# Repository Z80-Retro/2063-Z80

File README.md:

# Retro Z80 CPU Board

This project was designed to run CP/M 2.2 from an SD card.  It should be an attainable goal for anyone that can solder through-hole parts to assemble it. Note that J10 is an optional header that allows a Sparkfun SD card breakout board [DEV-13743](https://www.digikey.com/en/products/detail/sparkfun-electronics/DEV-13743/5881845) to used instead of soldering on the surface-mount SD socket part.

Here is an easy-to-find direct link to the [PDF of the schematic](https://github.com/Z80-Retro/2063-Z80/raw/main/2063-Z80.pdf) for a quick view.

## Where to get Boards & Software

* You can order boards from any prototype PCB vendor.  For example, I show how you can order these boards from [JLCPCB](https://jlcpcb.com/) or [OSHPark](https://oshpark.com/) by uploading the gerber files found in the releases of this and the flash programmer projects as shown in this [Z80 Retro! - How To Order PC Boards](https://youtu.be/AUg_sbPnzn0) video on YouTube.
  - Gerber files for the CPU board: [2063-Z80-v3](https://github.com/johnwinans/2063-Z80/releases/download/v3/2063-Z80-gerbers.zip)
  - Gerber files for the FLASH programmer: [2065-Z80-programmer-v2](https://github.com/johnwinans/2065-Z80-programmer/releases/download/v2.0/2065-Z80-programmer-gerbers.zip) (This is used with a Raspberry PI to program the FLASH chip on the CPU board.)

* Software for this project can be found in my [2063-Z80-cpm](https://github.com/johnwinans/2063-Z80-cpm) repo.

* Note that the [FLASH programmer](https://github.com/johnwinans/2065-Z80-programmer) has been designed to work with a Raspberry PI in the event that you don't already own such programmer.  This companion programmer PCB should cost about $2 more when it is ordered at the same time as the CPU board from JLCPCB or other similar proto-board shops as shown in the [Z80 Retro! - How To Order PC Boards](https://youtu.be/AUg_sbPnzn0) video on YouTube.

## Links to Related Material

* A youtube playlist discussing this project and how to build your own can be found in [John's Basement](https://www.youtube.com/watch?v=oekucjDcNbA&list=PL3by7evD3F51Cf9QnsAEdgSQ4cz7HQZX5)
* A PDF version of the schematic can be found [here](2063-Z80.pdf).
* Here is the as-built [BOM](2063-Z80.md) with links to the datasheets for all the parts.
* Here is another [BOM](2063-Z80-sockets.md) with links to sockets for the chips.
* To configure a new PI for use with this programmer board as well as to develop Z80 code 
for the Z80 Retro board, see this [PI Setup Guide](https://github.com/johnwinans/raspberry-pi-install)
* More software for this project will be added as it evolves.

## Links to Related Datasheets Seen On YouTube

* [Z80 Datasheet PS0178](https://www.zilog.com/docs/z80/ps0178.pdf) with detailed timing diagrams.
* [Z80 User Manual UM0080](http://www.zilog.com/docs/z80/um0080.pdf) with detailed descriptions of each instruction.
* [Z80 Assembly Language Programming Manual](http://zxevo.ru/inc/Zilog_Z80_assembly_language_programming_classic.pdf) - The original version of the instructions without the OCR errors present in UM0080.
* [Z80 CPU Peripherals User Manual UM0081](http://www.zilog.com/docs/z80/um0081.pdf) discusses the CTC and SIO.
* [Z80 Family Product Specifications Handbook - 1984](http://www.bitsavers.org/components/zilog/z80/Z80_Family_Product_Specifications_Handbook_Feb84.pdf) has nicer pictures of the SIO registers.
* [Wikipedia UART Article](https://en.wikipedia.org/wiki/Universal_asynchronous_receiver-transmitter)
* [AY-3-1015D UART Datasheet](https://rocelec.widen.net/view/pdf/bvesdj0cqf/GSIIS01845-1.pdf) (Has a discussion of the 16X bit-rate clock with diagrams etc. applicable to all UARTs.)

## Serial Port Cable Parts

* [How to make IDC cables](https://youtu.be/gZ420Z-8HuU) for the serial ports.
* [IDC 2x5 connectors](https://www.amazon.com/gp/product/B07S1NFG4S)
* [IDC D-SUB 9-pin connectors (Digikey)](https://www.digikey.com/en/products/detail/assmann-wsw-components/A-DSF-09LPIII-Z/924263)
* [IDC D-SUB 9-pin connectors (Amazon)](https://www.amazon.com/Uxcell-a15030600ux0494-Female-Connector-Ribbon/dp/B00YM41NTW)

## Parallel Port Cable Parts

* [IDC 2x13 connectors](https://www.amazon.com/gp/product/B07RXK96GV)
* [IDC D-SUB 25-pin connectors (Digikey)](https://www.digikey.com/en/products/detail/amphenol-icc-commercial-products/L17DBFRA25S/1972210)
* [IDC D-SUB 25-pin connectors (Amazon)](https://www.amazon.com/Fielect-Female-Adapter-Connector-Ribbon/dp/B082GMDNTS)

## Ribbon Cable

* [40-conductor (Amazon)](https://www.amazon.com/Eowpower-40Pin-40Way-Rainbow-Ribbon/dp/B079KQ6K3Y) - peel off a
 26-pin strip and a 10-pin strip to make one parallel and one serial cable (cut the 10-pin strip in half length-wise to make two serial cables.

# Release Notes

## V4.4.0

- Change footprint for SD socket to increase the pad size for mounting the case.
- Label R15 and R16 as DNP.
- Move the [diffs](./diffs/) into their own directory.
- V4.3.3 to V4.4.0 schematic [visual diff](https://github.com/Z80-Retro/2063-Z80/raw/main/diffs/2063-Z80-V4.3.3-V4.4.0-delta-schematic.pdf)
- V4.3.3 to V4.4.0 PCB [visual diff](https://raw.githubusercontent.com/Z80-Retro/2063-Z80/main/diffs/2063-Z80-V4.3.3-V4.4.0-delta-pcb.png)

## V4.3.3

- Increase the values of the RS232 charge pump (on U12) capacitors to improve filtering.
- V4.3.2 V4.3.3 schematic [visual diff](https://github.com/Z80-Retro/2063-Z80/raw/main/diffs/2063-Z80-V4.3.2-V4.3.3-delta-schematic.pdf)
- V4.3.2 V4.3.3 PCB [visual diff](https://github.com/Z80-Retro/2063-Z80/raw/main/diffs/2063-Z80-V4.3.2-V4.3.3-delta-pcb.png) (no changes)

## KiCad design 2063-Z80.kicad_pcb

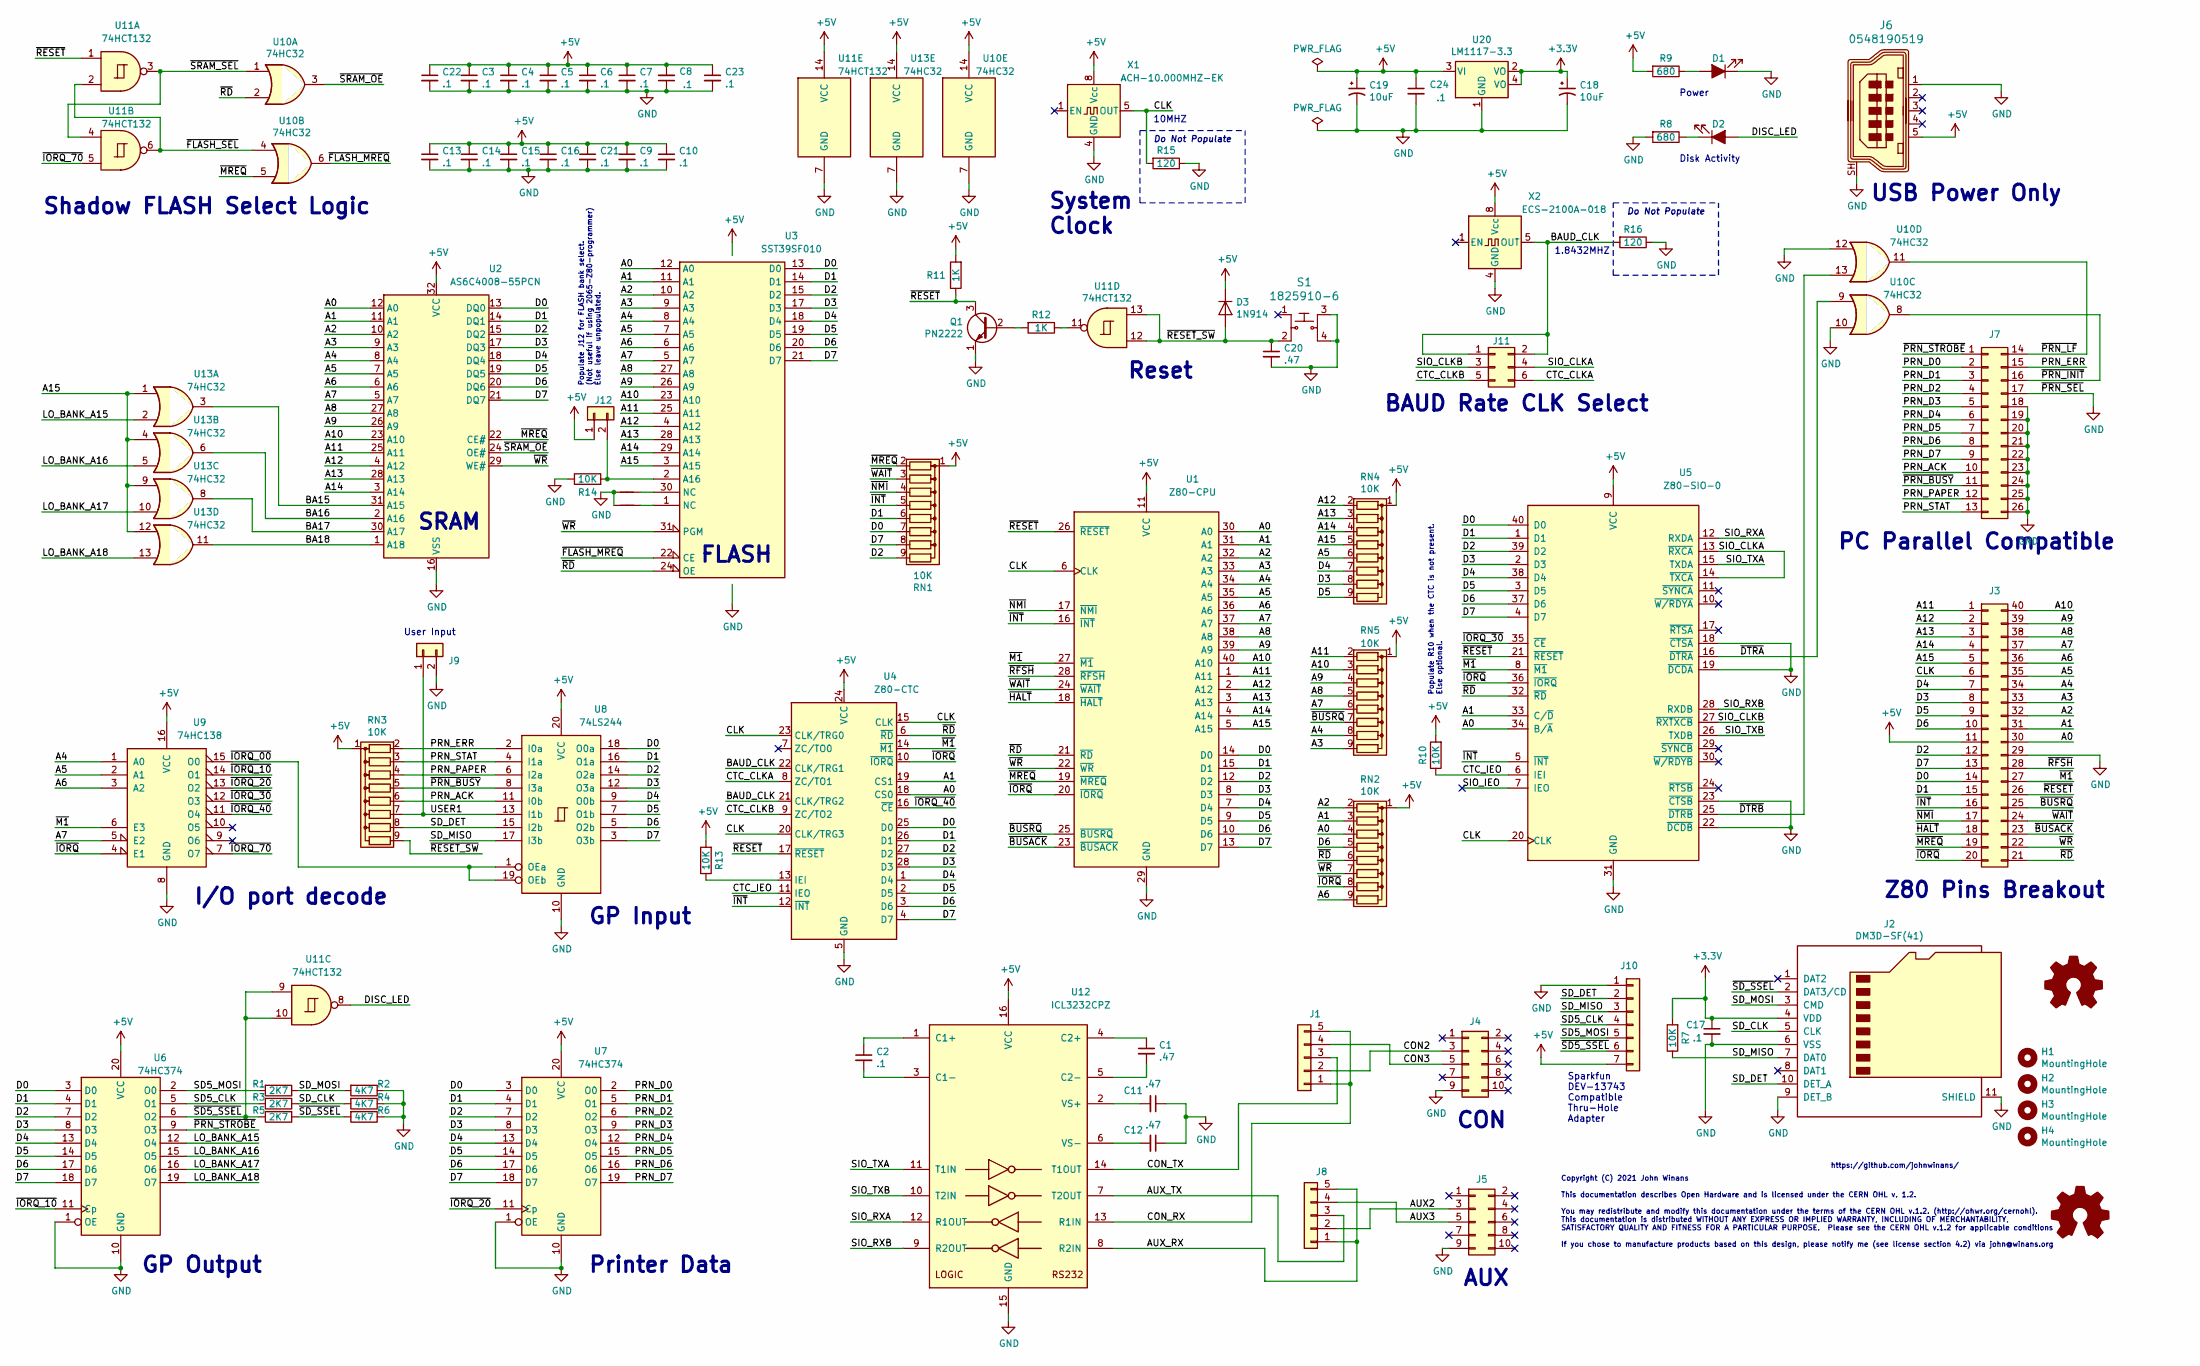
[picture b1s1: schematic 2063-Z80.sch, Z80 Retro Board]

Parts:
C1, C11, C12, C20: .47; C_Disc_D3.0mm_W2.0mm_P2.50mm; MPN C315C474K5R5TA7303; Digi-Key_PN 399-14039-1-ND
C2, C3, C4, C5, C6, C7, C8, C9, C10, C13, C14, C15, C16, C21, C22, C23: .1; C_Disc_D3.0mm_W2.0mm_P2.50mm; MPN ‎C315C104M5U5TA7303‎; Digi-Key_PN 399-9859-1-ND
C17: .1; C_0805_2012Metric_Pad1.18x1.45mm_HandSolder; MPN CL10B104KB8NNWC; Digi-Key_PN 1276-1935-1-ND
C18: 10uF; C_0805_2012Metric_Pad1.18x1.45mm_HandSolder; MPN CL21A106MQFNNNE; Digi-Key_PN 1276-1298-1-ND
C19: 10uF; CP_Radial_D5.0mm_P2.50mm; MPN ECE-A1EKS100; Digi-Key_PN P975-ND
C24: .1; C_0805_2012Metric_Pad1.15x1.40mm_HandSolder; MPN CL10B104KB8NNWC; Digi-Key_PN 1276-1935-1-ND
D1, D2: LED_ALT; LED_D3.0mm; MPN MV57640; Digi-Key_PN 1080-1122-ND
D3: 1N914; D_DO-35_SOD27_P7.62mm_Horizontal; MPN 1N4148TR; Digi-Key_PN 1N4148FSCT-ND
H1, H2, H3, H4: MountingHole; MountingHole_2.7mm
J1, J8: Conn_01x05; PinHeader_1x05_P2.54mm_Vertical; MPN PRPC005SAAN-RC; Digi-Key_PN S1011EC-05-ND
J2: DM3D-SF(41); microSD_HC_Hirose_DM3D-SF-bigpad; MPN ‎DM3D-SF(41)‎; Digi-Key_PN H126097CT-ND (alternate: 114-00841-68-1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
J3: Conn_02x20; PinHeader_2x20_P2.54mm_Vertical_counterclock; MPN PRPC020DAAN-RC; Digi-Key_PN S2011EC-20-ND
J4, J5: Conn_02x05; PinHeader_2x05_P2.54mm_Vertical; MPN PR20205VBDN; Digi-Key_PN 1849-1002-ND
J6: 0548190519; USB_Mini_B_Female_548190519; MPN 0548190519; Digi-Key_PN A135698-ND
J7: Conn_02x13; PinHeader_2x13_P2.54mm_Top_Bottom; MPN PRPC013DAAN-RC; Digi-Key_PN S2011EC-13-ND
J9, J12: Conn_01x02; PinHeader_1x02_P2.54mm_Vertical; MPN PRPC002SAAN-RC; Digi-Key_PN S1011EC-02-ND
J10: Conn_01x07; PinHeader_1x07_P2.54mm_Vertical; MPN PRPC007SAAN-RC; Digi-Key_PN S1011EC-07-ND
J11: Conn_02x03; PinHeader_2x03_P2.54mm_Vertical; MPN PH2-06-UA; Digi-Key_PN 2057-PH2-06-UA-ND
LOGO1: OSHW_Logo; OSHW-Logo_11.4x12mm_SilkScreen
LOGO2: OSHW_Logo; OSHW-Logo_5.7x6mm_SilkScreen
NT1, NT2: Net-Tie_2; NetTie-2_SMD_Pad0.5mm
Q1: PN2222; TO-92L; MPN PN2222A PBFREE; Digi-Key_PN 1514-PN2222APBFREE-ND
R1, R3, R5: 2K7; R_Axial_DIN0204_L3.6mm_D1.6mm_P5.08mm_Horizontal; MPN ‎CF18JT2K70‎; Digi-Key_PN CF18JT2K70CT-ND
R2, R4, R6: 4K7; R_Axial_DIN0204_L3.6mm_D1.6mm_P5.08mm_Horizontal; MPN ‎CF18JT4K70‎; Digi-Key_PN CF18JT4K70CT-ND
R7, R10, R13, R14: 10K; R_Axial_DIN0204_L3.6mm_D1.6mm_P5.08mm_Horizontal; MPN CF18JT10K0; Digi-Key_PN CF18JT10K0CT-ND
R8, R9: 680; R_Axial_DIN0204_L3.6mm_D1.6mm_P5.08mm_Horizontal; MPN ‎CF18JT680R‎; Digi-Key_PN CF18JT680RCT-ND‎
R11, R12: 1K; R_Axial_DIN0204_L3.6mm_D1.6mm_P5.08mm_Horizontal; MPN ‎CF18JT1K00‎; Digi-Key_PN CF18JT1K00CT-ND‎
R15, R16: 120; R_Axial_DIN0204_L3.6mm_D1.6mm_P5.08mm_Horizontal; MPN CF18JT120R; Digi-Key_PN CF18JT120RCT-ND
RN1, RN2, RN3, RN4, RN5: 10K; R_Array_SIP9; MPN ‎4609X-101-103LF‎; Digi-Key_PN 4609X-101-103LF-ND‎
S1: 1825910-6; Switch_Tactile_THT_6x6mm; MPN 1825910-6; Digi-Key_PN 450-1650-ND
U1: Z80-CPU; DIP-40_W15.24mm_Socket; MPN Z84C0010PEG‎; Digi-Key_PN 269-3898-ND
U2: AS6C4008-55PCN; DIP-32_W15.24mm_Socket; MPN AS6C4008-55PIN; Digi-Key_PN 1450-1178-5-ND‎
U3: SST39SF010; DIP-32_W15.24mm_Socket; MPN SST39SF010A-70-4C-PHE; Digi-Key_PN SST39SF010A-70-4C-PHE-ND‎
U4: Z80-CTC; DIP-28_W15.24mm_Socket; MPN Z84C3010PEG‎; Digi-Key_PN 269-3914-ND
U5: Z80-SIO-0; DIP-40_W15.24mm_Socket; MPN Z84C4010PEG‎; Digi-Key_PN 269-5062-ND‎
U6, U7: 74HC374; DIP-20_W7.62mm_Socket; MPN CD74HC374E; Digi-Key_PN 296-12806-5-ND
U8: 74LS244; DIP-20_W7.62mm_Socket; MPN SN74LS244NE4; Digi-Key_PN 296-36148-5-ND
U9: 74HC138; DIP-16_W7.62mm_Socket; MPN SN74HC138AN; Digi-Key_PN 296-SN74HC138AN-ND
U10, U13: 74HC32; DIP-14_W7.62mm_Socket; MPN CD74HC32E; Digi-Key_PN 296-12803-5-ND
U11: 74HCT132; DIP-14_W7.62mm_Socket; MPN CD74HCT132E; Digi-Key_PN 296-2090-5-ND
U12: ICL3232CPZ; DIP-16_W7.62mm_Socket; MPN ‎ICL3232CPZ‎; Digi-Key_PN ICL3232CPZ-ND‎
U20: LM1117-3.3; SOT-223; MPN NCP1117ST33T3G; Digi-Key_PN NCP1117ST33T3GOSCT-ND
X1: ACH-10.000MHZ-EK; Oscillator_DIP-8_combo; MPN ACH-10.000MHZ-EK; Digi-Key_PN 535-9167-5-ND
X2: ECS-2100A-018; Oscillator_DIP-8_combo; MPN ‎ECS-2100A-018‎; Digi-Key_PN XC231-ND‎

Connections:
+3V3: C17.1, C18.1, J2.4 (VDD), R7.2, U20.2 (VO), U20.4 (VO)
+5V: C3.1, C4.1, C5.1, C6.1, C7.1, C8.2, C9.1, C10.1, C13.1, C14.1, C15.1, C16.1, C19.1, C21.1, C22.1, C23.1, C24.1, D3.1 (K), J3.11, J6.5, J10.7, J12.1, R9.2, R10.2, R11.2, R13.2, RN1.1 (common), RN2.1 (common), RN3.1 (common), RN4.1 (common), RN5.1 (common), U1.11 (VCC), U2.32 (VCC), U3.32 (VCC), U4.24 (VCC), U5.9 (VCC), U6.20 (VCC), U7.20 (VCC), U8.20 (VCC), U9.16 (VCC), U10.14 (VCC), U11.14 (VCC), U12.16 (VCC), U13.14 (VCC), U20.3 (VI), X1.8 (Vcc), X2.8 (Vcc)
/A0: J3.30, RN2.4 (R3), U1.30 (A0), U2.12 (A0), U3.12 (A0), U4.18 (CS0), U5.34 (B/~A)
/A1: J3.31, RN2.3 (R2), U1.31 (A1), U2.11 (A1), U3.11 (A1), U4.19 (CS1), U5.33 (C/~D)
/A2: J3.32, RN2.2 (R1), U1.32 (A2), U2.10 (A2), U3.10 (A2)
/A3: J3.33, RN5.9 (R8), U1.33 (A3), U2.9 (A3), U3.9 (A3)
/A4: J3.34, RN5.8 (R7), U1.34 (A4), U2.8 (A4), U3.8 (A4), U9.1 (A0)
/A5: J3.35, RN4.6 (R5), U1.35 (A5), U2.7 (A5), U3.7 (A5), U9.2 (A1)
/A6: J3.36, RN2.9 (R8), U1.36 (A6), U2.6 (A6), U3.6 (A6), U9.3 (A2)
/A7: J3.37, RN5.6 (R5), U1.37 (A7), U2.5 (A7), U3.5 (A7), U9.5 (E2)
/A8: J3.38, RN5.5 (R4), U1.38 (A8), U2.27 (A8), U3.27 (A8)
/A9: J3.39, RN5.4 (R3), U1.39 (A9), U2.26 (A9), U3.26 (A9)
/A10: J3.40, RN5.3 (R2), U1.40 (A10), U2.23 (A10), U3.23 (A10)
/A11: J3.1, RN5.2 (R1), U1.1 (A11), U2.25 (A11), U3.25 (A11)
/A12: J3.2, RN4.2 (R1), U1.2 (A12), U2.4 (A12), U3.4 (A12)
/A13: J3.3, RN4.3 (R2), U1.3 (A13), U2.28 (A13), U3.28 (A13)
/A14: J3.4, RN4.4 (R3), U1.4 (A14), U2.3 (A14), U3.29 (A14)
/A15: J3.5, RN4.5 (R4), U1.5 (A15), U3.3 (A15), U13.1, U13.4, U13.9, U13.12
/AUX2: J5.3, J8.2
/AUX3: J5.5, J8.4
/AUX_RX: J8.1, J8.5, U12.8 (R2IN)
/AUX_TX: J8.3, U12.7 (T2OUT)
/BA15: U2.31 (A15), U13.3
/BA16: U2.2 (A16), U13.6
/BA17: U2.30 (A17), U13.8
/BA18: U2.1 (A18), U13.11
/BAUD_CLK: J11.1, J11.2, R16.2, U4.21 (CLK/TRG2), U4.22 (CLK/TRG1), X2.5 (OUT)
/CLK: J3.6, R15.2, U1.6 (CLK), U4.15 (CLK), U4.20 (CLK/TRG3), U4.23 (CLK/TRG0), U5.20 (CLK), X1.5 (OUT)
/CON2: J1.2, J4.3
/CON3: J1.4, J4.5
/CON_RX: J1.1, J1.5, U12.13 (R1IN)
/CON_TX: J1.3, U12.14 (T1OUT)
/CTC_CLKA: J11.6, U4.8 (ZC/TO1)
/CTC_CLKB: J11.5, U4.9 (ZC/TO2)
/CTC_IEO: R10.1, U4.11 (IEO), U5.6 (IEI)
/D0: J3.14, RN1.7 (R6), U1.14 (D0), U2.13 (DQ0), U3.13 (D0), U4.25 (D0), U5.40 (D0), U6.3 (D0), U7.3 (D0), U8.18 (O0a)
/D1: J3.15, RN1.6 (R5), U1.15 (D1), U2.14 (DQ1), U3.14 (D1), U4.26 (D1), U5.1 (D1), U6.4 (D1), U7.4 (D1), U8.16 (O1a)
/D2: J3.12, RN1.9 (R8), U1.12 (D2), U2.15 (DQ2), U3.15 (D2), U4.27 (D2), U5.39 (D2), U6.7 (D2), U7.7 (D2), U8.14 (O2a)
/D3: J3.8, RN4.8 (R7), U1.8 (D3), U2.17 (DQ3), U3.17 (D3), U4.28 (D3), U5.2 (D3), U6.8 (D3), U7.8 (D3), U8.12 (O3a)
/D4: J3.7, RN4.7 (R6), U1.7 (D4), U2.18 (DQ4), U3.18 (D4), U4.1 (D4), U5.38 (D4), U6.13 (D4), U7.13 (D4), U8.9 (O0b)
/D5: J3.9, RN4.9 (R8), U1.9 (D5), U2.19 (DQ5), U3.19 (D5), U4.2 (D5), U5.3 (D5), U6.14 (D5), U7.14 (D5), U8.7 (O1b)
/D6: J3.10, RN2.5 (R4), U1.10 (D6), U2.20 (DQ6), U3.20 (D6), U4.3 (D6), U5.37 (D6), U6.17 (D6), U7.17 (D6), U8.5 (O2b)
/D7: J3.13, RN1.8 (R7), U1.13 (D7), U2.21 (DQ7), U3.21 (D7), U4.4 (D7), U5.4 (D7), U6.18 (D7), U7.18 (D7), U8.3 (O3b)
/DISC_LED: D2.2 (A), U11.8
/LO_BANK_A15: U6.12 (O4), U13.2
/LO_BANK_A16: U6.15 (O5), U13.5
/LO_BANK_A17: U6.16 (O6), U13.10
/LO_BANK_A18: U6.19 (O7), U13.13
/PRN_ACK: J7.10, RN3.6 (R5), U8.11 (I0b)
/PRN_D0: J7.2, U7.2 (O0)
/PRN_D1: J7.3, U7.5 (O1)
/PRN_D2: J7.4, U7.6 (O2)
/PRN_D3: J7.5, U7.9 (O3)
/PRN_D4: J7.6, U7.12 (O4)
/PRN_D5: J7.7, U7.15 (O5)
/PRN_D6: J7.8, U7.16 (O6)
/PRN_D7: J7.9, U7.19 (O7)
/PRN_ERR: J7.15, RN3.2 (R1), U8.2 (I0a)
/PRN_PAPER: J7.12, RN3.4 (R3), U8.6 (I2a)
/PRN_STAT: J7.13, RN3.3 (R2), U8.4 (I1a)
/SD5_CLK: J10.4, R3.2, U6.5 (O1)
/SD5_MOSI: J10.5, R1.2, U6.2 (O0)
/SD_CLK: J2.5 (CLK), R3.1, R4.2
/SD_DET: J2.10 (DET_A), J10.2, RN3.8 (R7), U8.15 (I2b)
/SD_MISO: J2.7 (DAT0), J10.3, R7.1, U8.17 (I3b)
/SD_MOSI: J2.3 (CMD), R1.1, R2.2
/SIO_CLKA: J11.4, U5.13 (~RXCA), U5.14 (~TXCA)
/SIO_CLKB: J11.3, U5.27 (~RXTXCB)
/SIO_IEO: U5.7 (IEO)
/SIO_RXA: U5.12 (RXDA), U12.12 (R1OUT)
/SIO_RXB: U5.28 (RXDB), U12.9 (R2OUT)
/SIO_TXA: U5.15 (TXDA), U12.11 (T1IN)
/SIO_TXB: U5.26 (TXDB), U12.10 (T2IN)
/USER1: J9.1, RN3.7 (R6), U8.13 (I1b)
/~BUSACK: J3.23, U1.23 (~BUSACK~)
/~BUSRQ: J3.25, RN5.7 (R6), U1.25 (~BUSRQ~)
/~DTRA: U5.16 (~DTRA), U10.9
/~DTRB: U5.25 (~DTRB), U10.13
/~FLASH_MREQ: U3.22 (CE), U10.6
/~FLASH_SEL: U10.4, U11.2, U11.6
/~HALT: J3.18, U1.18 (~HALT~)
/~INT: J3.16, RN1.5 (R4), U1.16 (~INT~), U4.12 (~INT), U5.5 (~INT)
/~IORQ: J3.20, RN2.8 (R7), U1.20 (~IORQ~), U4.10 (~IORQ), U5.36 (~IORQ), U9.4 (E1)
/~IORQ_00: U8.1 (OEa), U8.19 (OEb), U9.15 (O0)
/~IORQ_10: U6.11 (Cp), U9.14 (O1)
/~IORQ_20: U7.11 (Cp), U9.13 (O2)
/~IORQ_30: U5.35 (~CE), U9.12 (O3)
/~IORQ_40: U4.16 (~CE), U9.11 (O4)
/~IORQ_70: U9.7 (O7), U11.5
/~M1: J3.27, U1.27 (~M1~), U4.14 (~M1), U5.8 (~M1), U9.6 (E3)
/~MREQ: J3.19, RN1.2 (R1), U1.19 (~MREQ~), U2.22 (CE#), U10.5
/~NMI: J3.17, RN1.4 (R3), U1.17 (~NMI~)
/~PRN_BUSY: J7.11, RN3.5 (R4), U8.8 (I3a)
/~PRN_INIT: J7.16, U10.8
/~PRN_LF: J7.14, U10.11
/~PRN_STROBE: J7.1, U6.9 (O3)
/~RD: J3.21, RN2.6 (R5), U1.21 (~RD~), U3.24 (OE), U4.6 (~RD), U5.32 (~RD), U10.2
/~RESET: J3.26, Q1.3 (C), R11.1, U1.26 (~RESET~), U4.17 (~RESET), U5.21 (~RESET), U11.1
/~RESET_SW: C20.1, D3.2 (A), RN3.9 (R8), S1.2, U11.12, U11.13
/~RFSH: J3.28, U1.28 (~RFSH~)
/~SD5_SSEL: J10.6, R5.2, U6.6 (O2), U11.9, U11.10
/~SD_SSEL: J2.2 (DAT3/CD), R5.1, R6.2
/~SRAM_OE: U2.24 (OE#), U10.3
/~SRAM_SEL: U10.1, U11.3, U11.4
/~WAIT: J3.24, RN1.3 (R2), U1.24 (~WAIT~)
/~WR: J3.22, RN2.7 (R6), U1.22 (~WR~), U2.29 (WE#), U3.31 (PGM)
GND: C3.2, C4.2, C5.2, C6.2, C7.2, C8.1, C9.2, C10.2, C11.1, C12.1, C13.2, C14.2, C15.2, C16.2, C17.2, C18.2, C19.2, C20.2, C21.2, C22.2, C23.2, C24.2, D1.1 (K), J2.6 (VSS), J2.9 (DET_B), J2.11 (SHIELD), J3.29, J4.9, J5.9, J6.1, J6.SH, J7.17, J7.18, J7.19, J7.20, J7.21, J7.22, J7.23, J7.24, J7.25, J7.26, J9.2, J10.1, NT1.1, NT2.1, Q1.1 (E), R2.1, R4.1, R6.1, R8.2, R14.1, R15.1, R16.1, S1.3, S1.4, U1.29 (GND), U2.16 (VSS), U3.16 (GND), U4.5 (GND), U5.18 (~CTSA), U5.19 (~DCDA), U5.22 (~DCDB), U5.23 (~CTSB), U5.31 (GND), U6.1 (OE), U6.10 (GND), U7.1 (OE), U7.10 (GND), U8.10 (GND), U9.8 (GND), U10.7 (GND), U10.10, U10.12, U11.7 (GND), U12.15 (GND), U13.7 (GND), U20.1 (GND), X1.4 (GND), X2.4 (GND)
unnamed: C1.1, U12.4 (C2+)
unnamed: C1.2, U12.5 (C2-)
unnamed: C2.1, U12.1 (C1+)
unnamed: C2.2, U12.3 (C1-)
unnamed: C11.2, U12.2 (VS+)
unnamed: C12.2, U12.6 (VS-)
unnamed: D1.2 (A), R9.1
unnamed: D2.1 (K), R8.1
unnamed: J12.2, R14.2, U3.2 (A16)
unnamed: NT1.2, U3.30 (NC)
unnamed: NT2.2, U3.1 (NC)
unnamed: Q1.2 (B), R12.2
unnamed: R12.1, U11.11
unnamed: R13.1, U4.13 (IEI)

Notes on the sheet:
Disk Activity
Power
USB Power Only
Z80 Pins Breakout
Shadow FLASH Select Logic
FLASH
SRAM
GP Input
GP Output
Printer Data
PC Parallel Compatible
1.8432MHZ
I/O port decode
CON
AUX
Copyright (C) 2021 John Winans This documentation describes Open Hardware and is licensed under the CERN OHL v. 1.2. You may redistribute and modify this documentation under the terms of the CERN OHL v.1.2. (http://ohwr.org/cernohl). This documentation is distributed WITHOUT ANY EXPRESS OR IMPLIED 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
Reset
10MHZ
https://github.com/johnwinans/
Sparkfun DEV-13743 Compatible Thru-Hole Adapter
BAUD Rate CLK Select
System Clock
Populate R10 when the CTC is not present. Else optional.
User Input
Populate J12 for FLASH bank select. (Not useful if using 2065-Z80-programmer) Else leave unpopulated.
Do Not Populate

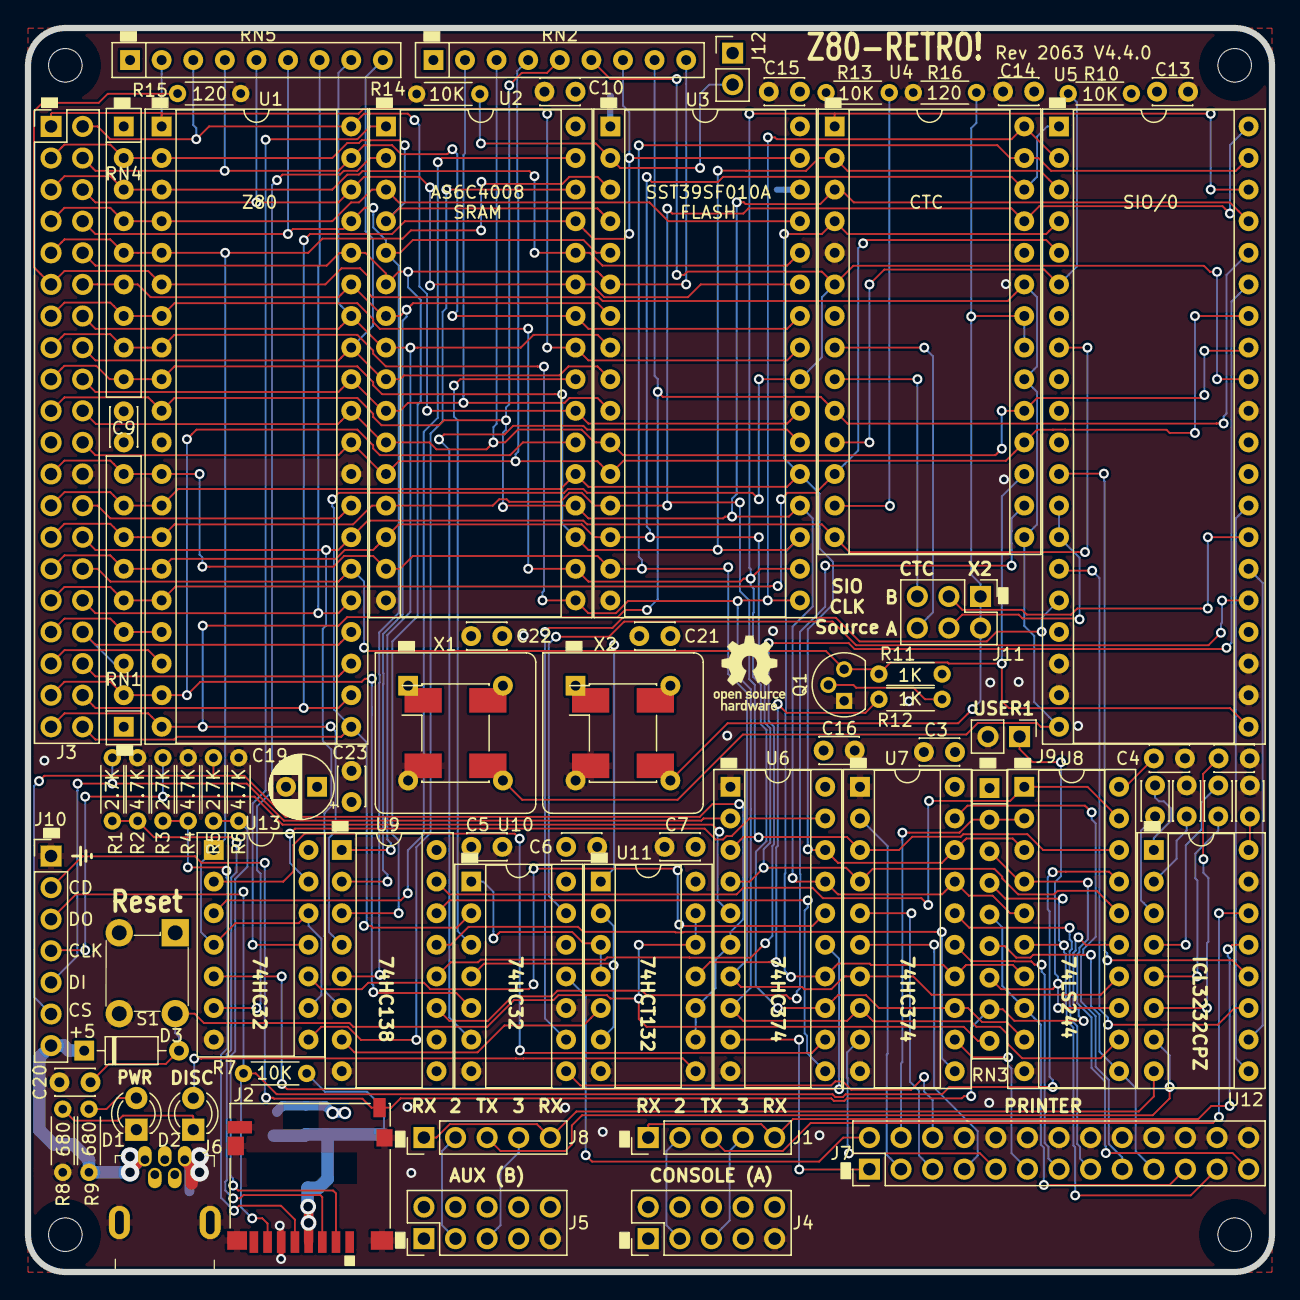
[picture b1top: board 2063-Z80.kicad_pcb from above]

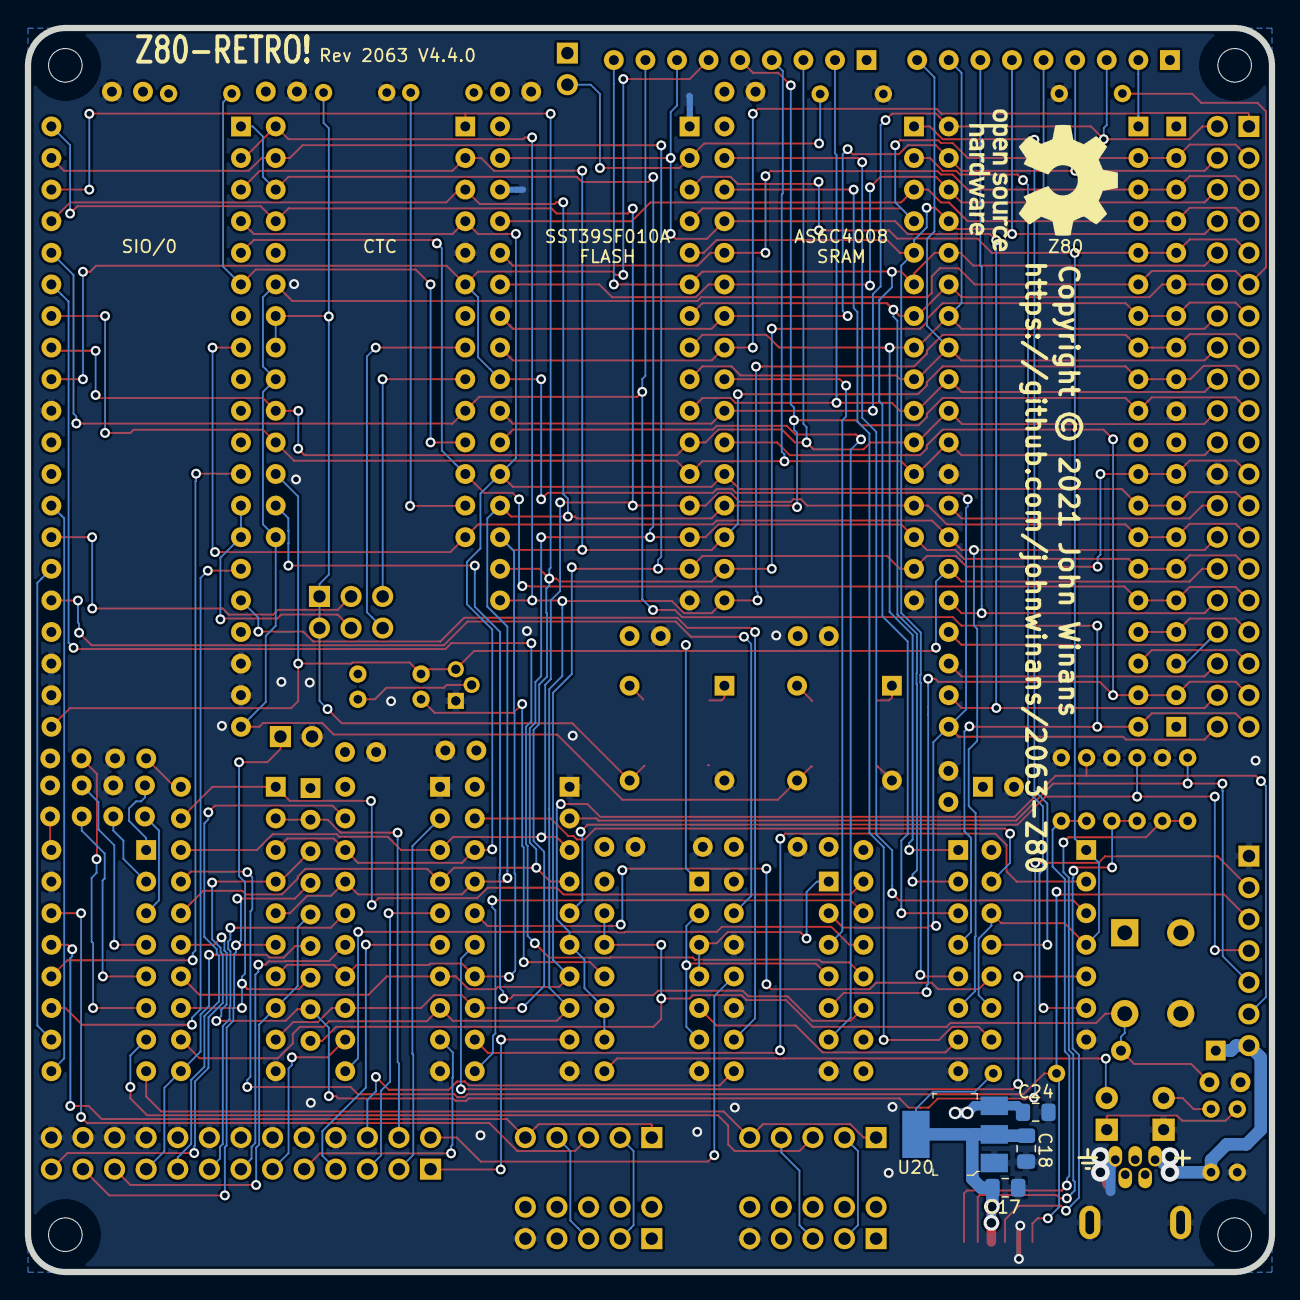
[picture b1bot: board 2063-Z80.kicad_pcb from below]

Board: 4 copper layers, 100.0 x 100.0 mm, 86 parts (7 on the bottom side), 120 nets.

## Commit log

2021-08-20 First release.
2021-08-24 BOM updates.
2021-09-04 Add jumpers for getting the SIO baud rate clock direct from X2 (EZ-bypass the CTC) Missing white-slug on J10 Show R8 & R9 as 680 ohms on silkscreen Change part number of the NAND gate to 74HCT132E (S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
2021-09-06 Add another 74LS32 for 512K memory support. Move 3.3v reg on back under the SD card. Use surface-mount caps for 3.3v power. Add alternate SMT footprints for X1 and X2.
2021-09-07 Update the PCB picture.
2021-09-07 Add part name to silk for U13.
2021-09-07 Move '32 to left on U13.
2021-09-08 Fix inverted DISC_LED signal. Create composite oscillator footprints for X1 and X2. Tidy up the sensitive clock-tracks.
2021-09-08 Freshened up the schematic PDF & 3D rendering.
2021-09-13 Change .1uF parts on BOM.
2021-09-15 Add pull up to SIO (and CTC) IEI.
2021-09-15 Slide J10 away from J3 as much as reasonable
2021-09-15 Add latest 3D pic.
2021-09-16 Ass USER1 jumper on an otherwise unused input.
2021-09-20 Change U11 symbol to a Schmitt NAND
2021-09-20 Tweak some part types in the BOM.
2021-09-20 Freshen up the gerber files.
2021-09-22 Freshen the schematic PDF
2021-10-08 Updated BOM to reflect the asbuilt Rev 3 board.
2021-10-09 Refresh schematic after BOM updates.
2021-10-13 Revise BOM to reflect the as-built board.
2021-10-13 Generate a BOM with clickable datasheet links
2021-10-13 OK.. html is annoying... lets try an MD file
2021-10-13 cleanups..
2021-10-13 try again..
2021-10-13 what is with github table markdown anyway?
2021-10-13 Try hyphens this time..
2021-10-13 Clean up BOM values & formatting
2021-10-13 add links to related parts
2021-10-19 Added a BOM of sockets.
2021-10-19 Add link to 2065-Z80-programmer
2021-10-19 spelling fix
2021-10-19 Bold link to FLASH programmer
    Bold the note about ordering the FLASH programmer at the same time as the Z80 board to save money
2021-10-29 Add blinky test apps
2021-10-30 Speed up the blink rate.
2021-10-30 Add a link to the Raspberry PI SD card install instructions.
2021-10-30 Add notes on installing z80asm and using the programmer
2021-11-10 Added SIO test app.
2021-11-10 More test cases
2021-11-12 Add hello_lpt2 to print small banners on an RX-80
2021-11-12 Set tab size to match my vim settings.
2021-11-12 Spelling correction
2021-11-14 Clean up names
2021-11-14 Doc cleanup.
2021-11-14 Add hello_sio2.asm to test SIO IRQs
2021-11-15 Channel reset during init.
2021-11-15 Add status affects vector.
2021-11-19 CLean up whitespace foolishness.
2021-12-01 Move ~PRN_LF from U5.17 to U5.25
2021-12-01 Ignore .OLD files
2021-12-01 Change C20 to .47uF to make RESET last 4X longer
2021-12-01 Add alternate source for SD socket.
2021-12-01 Make pins U3.1 & U3.30 NC (easier for UV EPROM)
2021-12-01 Add pulldown & J12 to A16 for FLASH bank select
2021-12-01 Clean up silkscreen.
2021-12-01 Added Rev4 gerbers
2021-12-01 Increase 5V copper to close thru-hole pads
2021-12-01 Add Rev4 PDF schematic.
2021-12-01 Terminate the clock traces.
2021-12-02 Keep more of the main CLK on on front layer
2021-12-07 Change comment because uptime is not in seconds.
2021-12-14 Make useful the datasheet for the '138
2021-12-15 Init CTC3 to 19200 & skip a line before printing
2021-12-15 Added conditional include for hendump
2021-12-16 Do not enable the SIO autoenables
2021-12-16 Add links to related datasheets
2021-12-16 Change link to use the Zilog site.
2021-12-16 Note why linking to AY-3-1015D
2021-12-16 Add links to IDC bits for serial & parallel cables
2021-12-16 Add Z80 datasheet.
2021-12-17 Rename file for consistency
2021-12-17 Add dependancies
2021-12-17 Add comments
2021-12-17 Stub in a line for running fast (as well as slow)
2021-12-17 Add example of a critical region of code
2021-12-18 Add doc & factor puts out of bank_select.asm
2021-12-18 Added status_gpio tester
2021-12-18 Remove commented-out code
2021-12-23 Rename hello_ctc.asm to hello_ctc2.asm
2021-12-23 Add hello_ctc1 example to run CTC sans IRQs
2021-12-23 Added another overstrike test patthern.
2021-12-29 Add more baud rates & a timer config
2022-01-07 Add note that CTC chan 0 vector is used for all
2022-01-19 Version shown on YouTube CTC video
2022-03-15 dd net ties to U3 for EZ-hacking
2022-03-15 Add link to CP/M software repo
2022-03-15 Remove the unused map files
2022-03-15 Add script to show diffs btw schematics & gerbers
2022-03-15 Checkout main (not head)
2022-03-15 Update v3-v4-diffs.sh to generate diff images cleanly
2022-03-15 Cleanup tmp after generate diffs Add diff images to repo
2022-03-17 Add links to the gerber files.
2022-03-17 Added Where to get Boards & Software
2022-03-22 Change silk screen on U11 from '00 to 74HCT132
2022-03-22 Added TTL serial header & power option.
2022-03-22 Remove gerbers (DO NOT BUILD)
2022-03-23 Add USB adapter
2022-03-23 Update PCB image & schematic
2022-03-23 Mark optional USB bits
2022-03-23 Added diffs for v4rc2
2022-06-20 Change silkscreen for official v4rc1a release
2022-06-20 Copy diff script from abandoned v4rc2.
2022-06-20 Release v4rc1a
2022-06-20 Remove the old v4 schematic delta
2022-06-21 Clean up git branch mess for version 4 :-(
2022-07-30 Change teh silkscreen label on U2 to AS6C4008
2022-07-30 Change U2 label on back silkscreen.
2022-07-30 Change the rev number in the silks too
2023-01-18 Add a link to old version of assy lang manual
    Add a link to an early edition of the Assembly Language Programming Manual that does not have the OCR scanning errors in it that are present in the later releases of it in UM0080.
2023-01-28 Added meta file so can sanely open as a template
2023-01-28 Change C1, 11 and 12 to .47uF
2023-02-11 Export PDF after cap value changes Change schematic rev to 4.3.1
2023-02-11 Fix inconsistent revision number & re-export PDF
2023-02-19 dennowiggle: change doc page number reference
2023-02-19 Get to schematic PDF sans githb fumbling
2023-03-29 Change Digikey numbers on 5-pin headers.
2023-04-20 Increase pad sizes on SD socket Label R15 and R16 as DNP Move the diffs into their own directory
2023-04-20 Add diffs for 4.3.3 -> 4.4.0
2023-04-20 Fix diff filename
2023-04-20 Add diff images from 4.3.3 to 4.4.0
2023-04-20 Move old diffs into new dir
2023-05-06 Add V4.3.2-V4.3.3-diffs.sh and images
2023-05-06 Added links to diffs in release notes

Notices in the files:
2063-Z80.kicad_pcb:
Copyright © 2021 John Winans
2063-Z80.sch:
If you chose to manufacture products based on this design, please notify me (see license section 4.2) via john@winans.org
